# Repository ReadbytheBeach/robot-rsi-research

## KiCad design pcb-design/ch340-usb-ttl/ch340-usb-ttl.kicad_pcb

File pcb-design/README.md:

# CH340C Type-C 转 3.3V TTL 转接板

30×30mm、双层、成品板厚 1.0mm、全部元件在顶面，普通自由走线使用斜线／45°转角。使用 CH340C 内部时钟，USB 5V 经 AP2112K 稳压为 3.3V。

TTL 使用 JST SUR 0.8mm 四针卧插连接器，焊盘编号依次为 **1＝3.3V、2＝TX、3＝RX、4＝GND**。TX／RX 以本板方向命名；连接目标时交叉接线。

## 下载与查看

- [完整 KiCad 9 工程 ZIP](CH340C_USB_TTL_30x30_RevA.zip?raw=true)：含可编辑工程、制造输出、BOM、模型、分析记录及说明。
- [工程目录](ch340-usb-ttl/)／[使用说明](ch340-usb-ttl/README.zh-CN.md)。
- [原理图 PDF](ch340-usb-ttl/exports/ch340-usb-ttl-schematic.pdf)。
- [Gerber 与钻孔 ZIP](ch340-usb-ttl/exports/CH340C_USB_TTL_RevA_Gerber.zip?raw=true)。
- [BOM](ch340-usb-ttl/BOM.csv)／[顶层贴片坐标](ch340-usb-ttl/exports/ch340-usb-ttl-top-pos.csv)。
- [设计审查](ch340-usb-ttl/REVIEW.zh-CN.md)／[制板要求](ch340-usb-ttl/FABRICATION.zh-CN.md)／[首板测试](ch340-usb-ttl/BRINGUP.zh-CN.md)。

解压完整工程，使用 KiCad 9 打开 `ch340-usb-ttl.kicad_pro`；保留同目录的本地符号和 `3dmodels/`。

预览已包含取得的 7 类官方 KiCad 模型；JST 卧插连接器与 PTC 的精确模型缺失，不能据此检查它们的机械干涉。

## 验证与制造条件

原生 ERC／DRC、未连接及原理图／PCB 一致性检查均为 0。USB 均匀差分干线按 90Ω 目标设计，名义计算约 89.859Ω；焊盘、换向分支和窄线过渡另计。投板前须由板厂按实际叠层确认阻抗，并核对所采购连接器的厂家尺寸图。

3.3V 外供预算建议不超过 50mA；此数值不是独立电子限流器。尚未进行实物枚举、回环、负载、EMC／ESD 或阻抗测量。完整边界见设计审查和使用说明。

第三方模型、计算代码及数据手册的来源和许可保存在工程内的 `NOTICE.md`、`3dmodels/`、`references/` 与 `datasheets/`。

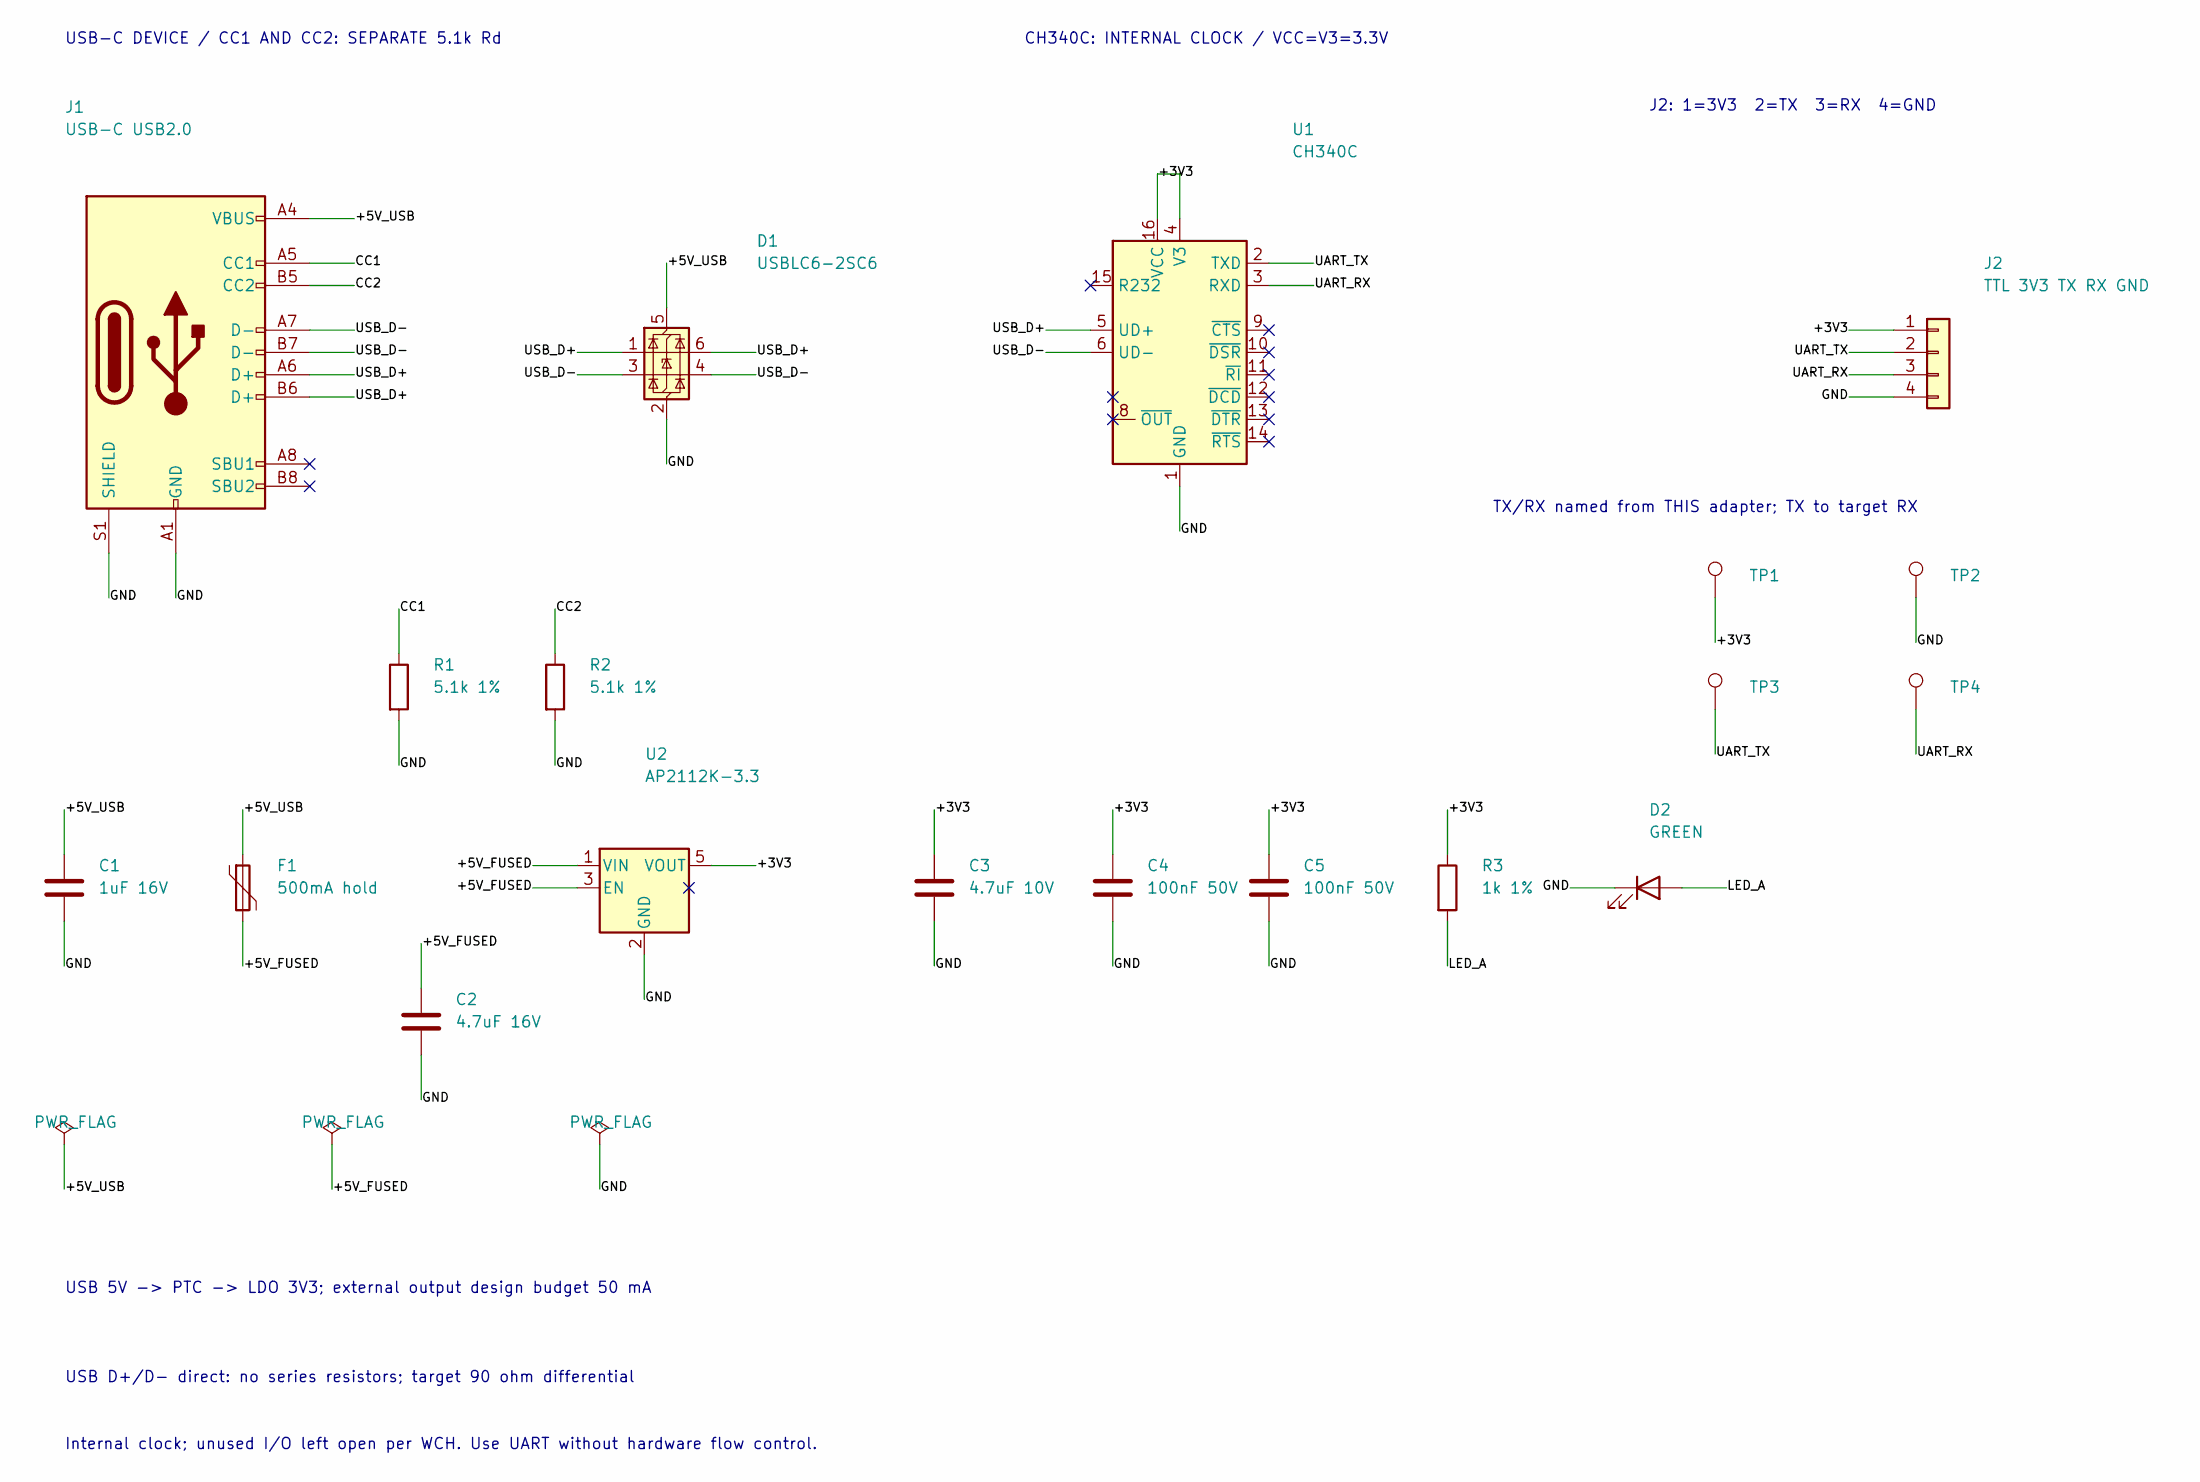
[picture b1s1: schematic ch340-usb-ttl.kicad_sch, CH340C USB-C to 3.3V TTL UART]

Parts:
C1: 1uF 16V; C_0603_1608Metric; MPN C1608X7R1C105K080AC
C2: 4.7uF 16V; C_0603_1608Metric; MPN C1608X5R1C475K080AC
C3: 4.7uF 10V; C_0603_1608Metric; MPN C1608X5R1A475K080AC
C4, C5: 100nF 50V; C_0603_1608Metric; MPN C1608X7R1H104K080AA
D1: USBLC6-2SC6; SOT-23-6; MPN USBLC6-2SC6
D2: GREEN; LED_0603_1608Metric; MPN LTST-C190KGKT
F1: 500mA hold; Fuse_1812_4532Metric; MPN MF-MSMF050-2
J1: USB-C USB2.0; USB_C_Receptacle_GCT_USB4105-xx-A_16P_TopMnt_Horizontal; MPN USB4105-GF-A
J2: TTL 3V3 TX RX GND; JST_SUR_SM04B-SURS-TF_1x04-1MP_P0.80mm_Horizontal; MPN SM04B-SURS-TF(LF)(SN)
R1, R2: 5.1k 1%; R_0603_1608Metric; MPN RC0603FR-075K1L
R3: 1k 1%; R_0603_1608Metric; MPN RC0603FR-071KL
TP1: +3V3; TestPoint_Pad_D1.0mm; MPN PCB TEST PAD
TP2: GND; TestPoint_Pad_D1.0mm; MPN PCB TEST PAD
TP3: UART_TX; TestPoint_Pad_D1.0mm; MPN PCB TEST PAD
TP4: UART_RX; TestPoint_Pad_D1.0mm; MPN PCB TEST PAD
U1: CH340C; SOIC-16_3.9x9.9mm_P1.27mm; MPN CH340C
U2: AP2112K-3.3; SOT-23-5; MPN AP2112K-3.3TRG1

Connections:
/+3V3: C3.1, C4.1, C5.1, J2.1, R3.1, TP1.1, U1.4 (V3), U1.16 (VCC), U2.5 (VOUT)
/+5V_FUSED: C2.1, F1.2, U2.1 (VIN), U2.3 (EN)
/+5V_USB: C1.1, D1.5 (VBUS), F1.1, J1.A4 (VBUS), J1.A9 (VBUS), J1.B4 (VBUS), J1.B9 (VBUS)
/CC1: J1.A5 (CC1), R1.1
/CC2: J1.B5 (CC2), R2.1
/GND: C1.2, C2.2, C3.2, C4.2, C5.2, D1.2 (GND), D2.1 (K), J1.A1 (GND), J1.A12 (GND), J1.B1 (GND), J1.B12 (GND), J1.S1 (SHIELD), J2.4, R1.2, R2.2, TP2.1, U1.1 (GND), U2.2 (GND)
/LED_A: D2.2 (A), R3.2
/UART_RX: J2.3, TP4.1, U1.3 (RXD)
/UART_TX: J2.2, TP3.1, U1.2 (TXD)
/USB_D+: D1.1 (I/O1), D1.6 (I/O1), J1.A6 (D+), J1.B6 (D+), U1.5 (UD+)
/USB_D-: D1.3 (I/O2), D1.4 (I/O2), J1.A7 (D-), J1.B7 (D-), U1.6 (UD-)

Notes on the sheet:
USB-C DEVICE / CC1 AND CC2: SEPARATE 5.1k Rd
CH340C: INTERNAL CLOCK / VCC=V3=3.3V
J2: 1=3V3 2=TX 3=RX 4=GND
TX/RX named from THIS adapter; TX to target RX
USB 5V -> PTC -> LDO 3V3; external output design budget 50 mA
USB D+/D- direct: no series resistors; target 90 ohm differential
Internal clock; unused I/O left open per WCH. Use UART without hardware flow control.

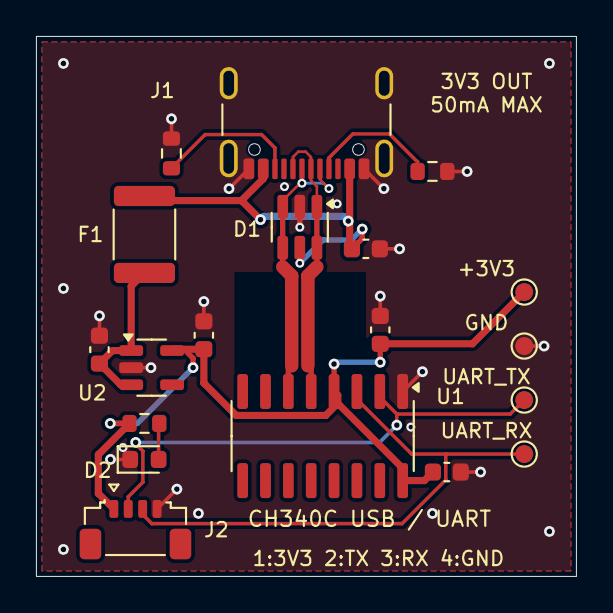
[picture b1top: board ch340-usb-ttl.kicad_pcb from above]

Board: 2 copper layers, 30.0 x 30.0 mm, 19 parts (0 on the bottom side), 11 nets.
